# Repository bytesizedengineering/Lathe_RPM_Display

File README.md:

# Lathe_RPM_Display

See project on YouTube: https://youtu.be/7gDZs0bImr0
I bought a wood lathe a few months ago and I thought it would be fun to make my own digital readout. 
The plan for this project was to use a hall effect sensor and a neodymium magnet to sense the rotations of the lathe spindle. 
I used an arduino board to read the sensor, count the pulses, and calculate the RPM of the spindle. 
I used seven segment displays to show the RPM reading. I designed a PCB and 3D printed an enclosure.

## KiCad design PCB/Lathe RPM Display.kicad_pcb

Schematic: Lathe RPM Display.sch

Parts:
A1: Arduino_Nano_v3.x; Arduino_Nano
J1: Conn_01x02; PinSocket_1x02_P2.54mm_Vertical
Q1: A3144EU; TO-92-3; MPN OH090U; Digi-Key_PN 365-1001-ND
Q2, Q3, Q4, Q5: 2N7000; TO-92_Inline
R1, R2, R3, R4, R5, R6, R7, R8: 470; R_0805_2012Metric_Pad1.15x1.40mm_HandSolder
R9: 10k; R_0805_2012Metric_Pad1.15x1.40mm_HandSolder
U1, U2, U3, U4: KCSC02-105; 7SegmentLED_LTS6760_LTS6780

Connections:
+5V: A1.30 (VIN), J1.2, Q1.1, R9.2
/A: A1.19 (A0), R1.2
/B: A1.20 (A1), R2.2
/C: A1.21 (A2), R3.2
/D: A1.22 (A3), R4.2
/DP: A1.15 (D12), R8.2
/E: A1.23 (A4), R5.2
/F: A1.24 (A5), R6.2
/G: A1.16 (D13), R7.2
GND: A1.4 (GND), A1.29 (GND), J1.1, Q1.2, Q2.1, Q3.1, Q4.1, Q5.1
unnamed: A1.5 (D2), Q1.3, R9.1
unnamed: A1.7 (D4), Q3.2
unnamed: A1.8 (D5), Q2.2
unnamed: A1.9 (D6), Q5.2
unnamed: A1.10 (D7), Q4.2
unnamed: Q2.3, U1.3, U1.8
unnamed: Q3.3, U2.3, U2.8
unnamed: Q4.3, U3.3, U3.8
unnamed: Q5.3, U4.3, U4.8
unnamed: R1.1, U1.7, U2.7, U3.7, U4.7
unnamed: R2.1, U1.6, U2.6, U3.6, U4.6
unnamed: R3.1, U1.4, U2.4, U3.4, U4.4
unnamed: R4.1, U1.2, U2.2, U3.2, U4.2
unnamed: R5.1, U1.1, U2.1, U3.1, U4.1
unnamed: R6.1, U1.9, U2.9, U3.9, U4.9
unnamed: R7.1, U1.10, U2.10, U3.10, U4.10
unnamed: R8.1, U1.5, U2.5, U3.5, U4.5

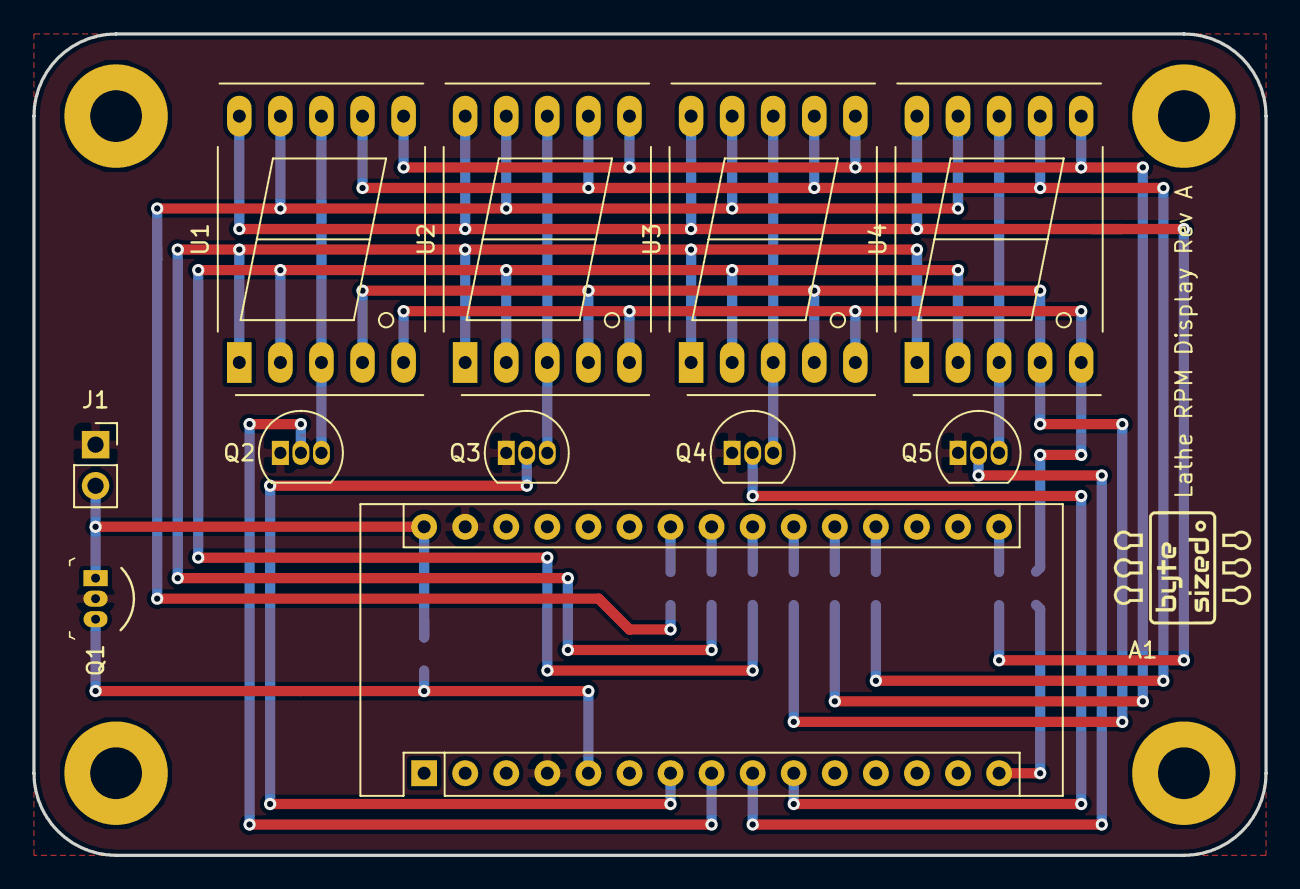
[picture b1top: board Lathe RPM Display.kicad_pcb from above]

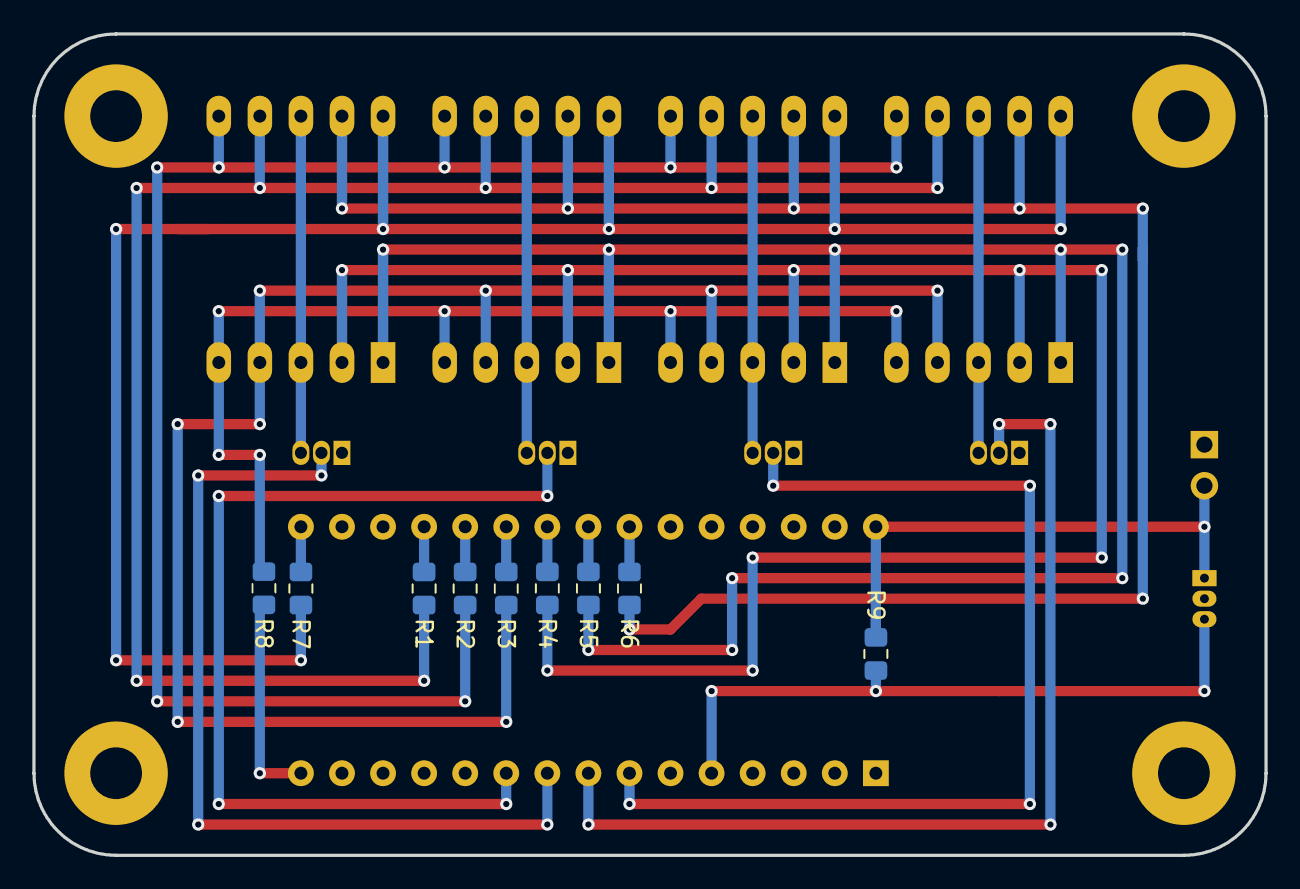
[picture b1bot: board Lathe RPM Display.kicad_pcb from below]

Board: 2 copper layers, 76.2 x 50.8 mm, 20 parts (9 on the bottom side), 27 nets.

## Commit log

2019-11-19 Initial PCB and Code upload
2019-11-19 Update LatheRPMDisplay.ino
    Loop through all seven segments on all four digits
2019-11-22 Update LatheRPMDisplay.ino
    Seven segment displays how many seconds since last reset
2019-11-24 code, schematic and layout
    Got code to a good working state. Schematic is good, maybe a couple more additions for power. Started layout and happy with locations. No traces routed.
2020-02-06 hall effect fix
    Adjusted pulses per revolution to fix hall effect sensor double pulse
